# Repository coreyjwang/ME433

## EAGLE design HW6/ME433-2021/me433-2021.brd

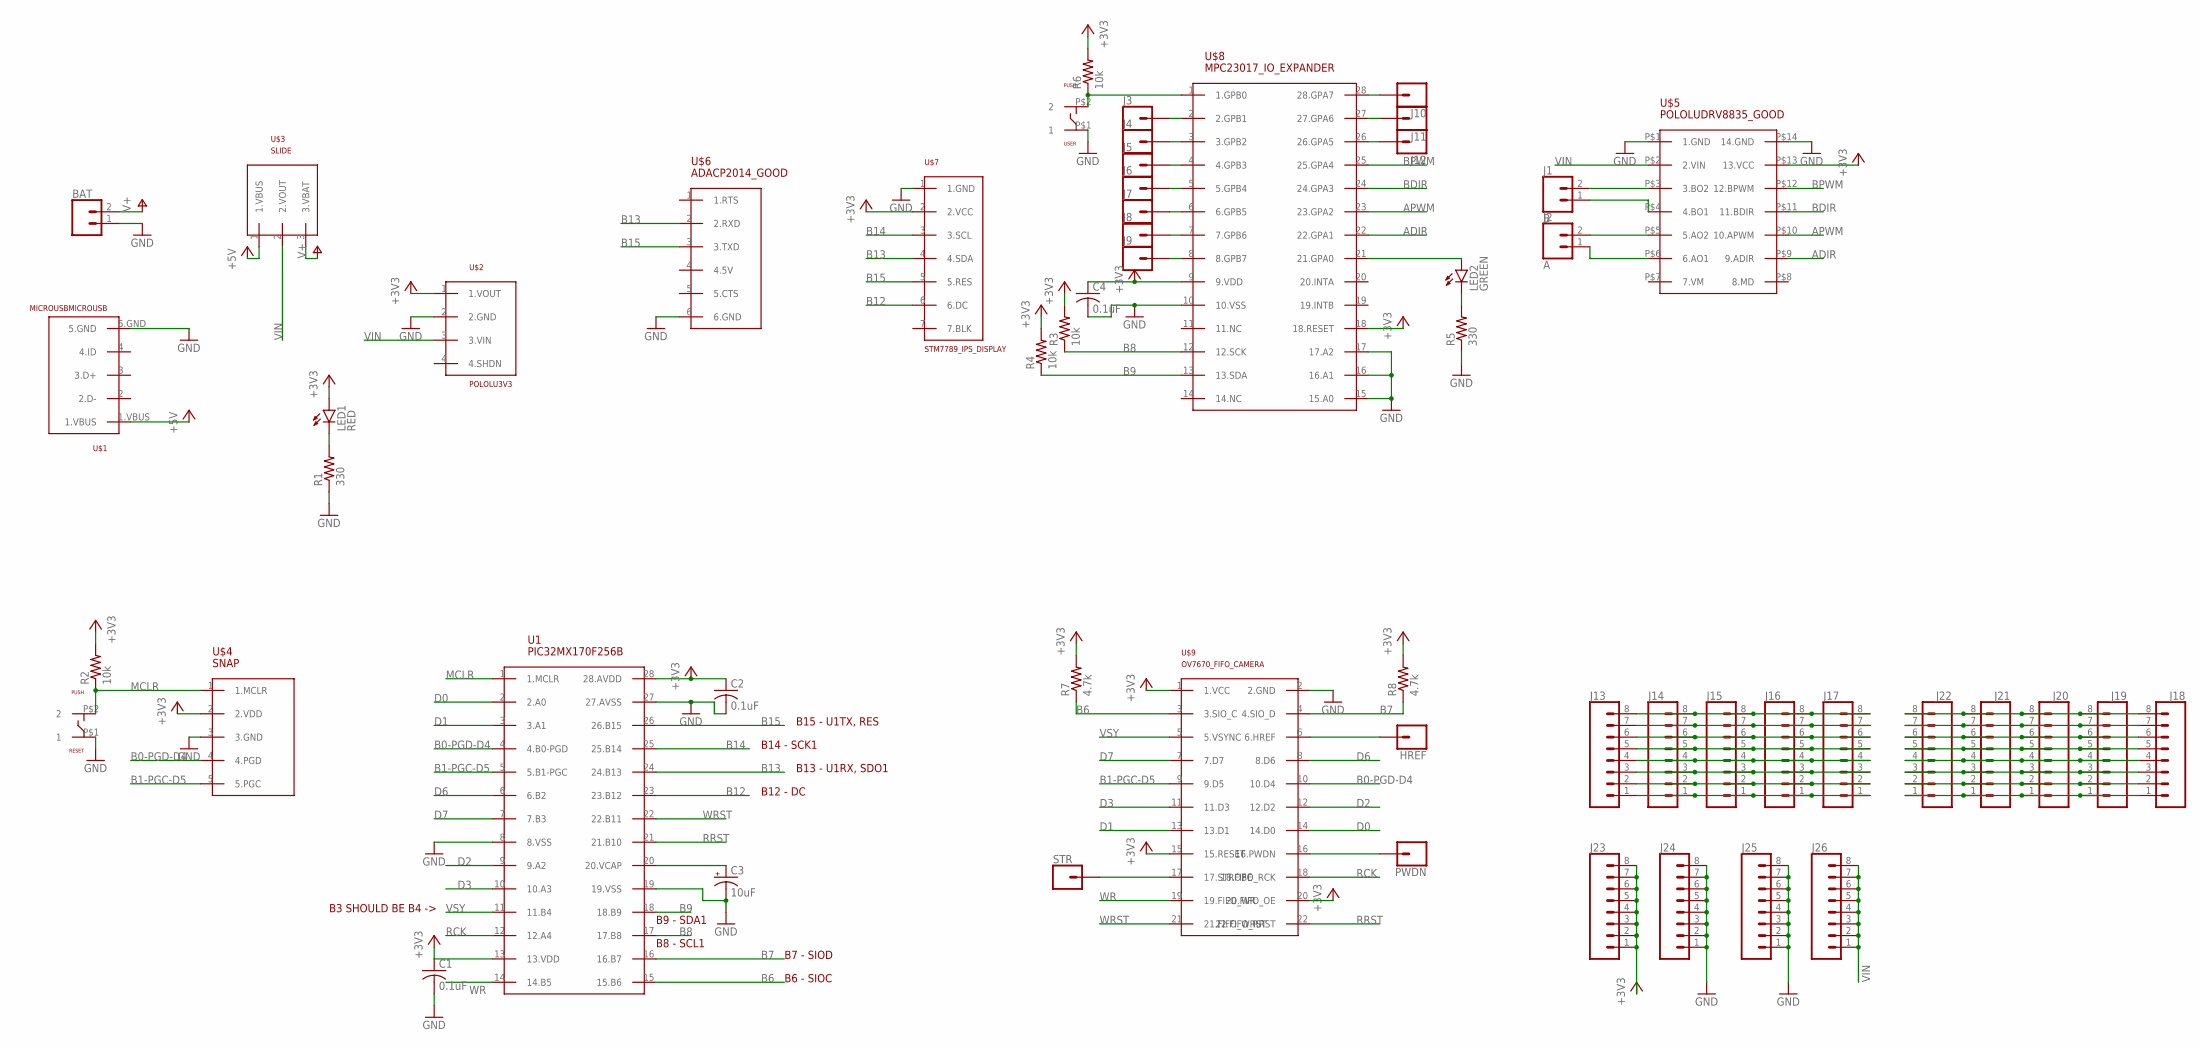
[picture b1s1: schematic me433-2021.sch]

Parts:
BAT: CONN_02; 1X02
C1, C2, C4: 0.1uF; C025-030X050
C3: 10uF; B45181B
HREF: CONN_01; 1X01
J1: B; 1X02
J2: A; 1X02
J3, J4, J5, J6, J7, J8, J9, J10, J11, J12: CONN_01; 1X01
J13, J14, J15, J16, J17, J18, J19, J20, J21, J22, J23, J24, J25, J26: CONN_08"; 1X08
LED1: RED; LED3MM
LED2: GREEN; LED3MM
PWDN: CONN_01; 1X01
R1, R5: 330; 0207/10
R2, R3, R4, R6: 10k; 0207/10
R7, R8: 4.7k; 0207/10
RESET: PUSH
STR: CONN_01; 1X01
U1: PIC32MX170F256B; DIL28-3
U$1: MICROUSBMICROUSB; MICROUSB
U$2: POLOLU3V3
U$3: SLIDE
U$4: SNAP; 1X05
U$5: POLOLUDRV8835_GOOD; POLOLU_DRV8835_H_BRIDGE_BREAKOUT
U$6: ADACP2014_GOOD; 1X06
U$7: STM7789_IPS_DISPLAY; 1X07
U$8: MPC23017_IO_EXPANDER; DIL28-3
U$9: OV7670_FIFO_CAMERA; 2X12
USER: PUSH

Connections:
+3V3: C2.1, C4.1, J23.1, J23.2, J23.3, J23.4, J23.5, J23.6, J23.7, J23.8, LED1.A, R2.2, R3.2, R4.2, R6.2, R7.2, R8.2, U1.28 (28.AVDD), U$2.1 (1.VOUT), U$4.2 (2.VDD), U$5.P$13 (13.VCC), U$7.2 (2.VCC), U$8.9 (9.VDD), U$8.18 (18.RESET), U$9.1 (1.VCC), U$9.15 (15.RESET), U$9.20 (20.FIFO_OE)
+5V: U$1.1.VBUS, U$3.1 (1.VBUS)
ADIR: U$5.P$9 (9.ADIR), U$8.22 (22.GPA1)
APWM: U$5.P$10 (10.APWM), U$8.23 (23.GPA2)
B0-PGD-D4: U1.4 (4.B0-PGD), U$4.4 (4.PGD), U$9.10 (10.D4)
B1-PGC-D5: U1.5 (5.B1-PGC), U$4.5 (5.PGC), U$9.9 (9.D5)
B6: R7.1, U1.15 (15.B6), U$9.3 (3.SIO_C)
B7: R8.1, U1.16 (16.B7), U$9.4 (4.SIO_D)
B8: R3.1, U1.17 (17.B8), U$8.12 (12.SCK)
B9: R4.1, U1.18 (18.B9), U$8.13 (13.SDA)
B12: U1.23 (23.B12), U$7.6 (6.DC)
B13: U1.24 (24.B13), U$6.2 (2.RXD), U$7.4 (4.SDA)
B14: U1.25 (25.B14), U$7.3 (3.SCL)
B15: U1.26 (26.B15), U$6.3 (3.TXD), U$7.5 (5.RES)
BDIR: U$5.P$11 (11.BDIR), U$8.24 (24.GPA3)
BPWM: U$5.P$12 (12.BPWM), U$8.25 (25.GPA4)
D0: U1.2 (2.A0), U$9.14 (14.D0)
D1: U1.3 (3.A1), U$9.13 (13.D1)
D2: U1.9 (9.A2), U$9.12 (12.D2)
D3: U1.10 (10.A3), U$9.11 (11.D3)
D6: U1.6 (6.B2), U$9.8 (8.D6)
D7: U1.7 (7.B3), U$9.7 (7.D7)
GND: BAT.1, C1.2, C2.2, C3.-, C4.2, J24.1, J24.2, J24.3, J24.4, J24.5, J24.6, J24.7, J24.8, J25.1, J25.2, J25.3, J25.4, J25.5, J25.6, J25.7, J25.8, R1.1, R5.1, RESET.P$1 (1), U1.8 (8.VSS), U1.19 (19.VSS), U1.27 (27.AVSS), U$1.5.GND, U$2.2 (2.GND), U$4.3 (3.GND), U$5.P$1 (1.GND), U$5.P$14 (14.GND), U$6.6 (6.GND), U$7.1 (1.GND), U$8.10 (10.VSS), U$8.15 (15.A0), U$8.16 (16.A1), U$8.17 (17.A2), U$9.2 (2.GND), USER.P$1 (1)
MCLR: R2.1, RESET.P$2 (2), U1.1 (1.MCLR), U$4.1 (1.MCLR)
unnamed: LED1.K (C), R1.2
unnamed: C1.1, U1.13 (13.VDD)
unnamed: C3.+, U1.20 (20.VCAP)
unnamed: J1.2, U$5.P$3 (3.BO2)
unnamed: J1.1, U$5.P$4 (4.BO1)
unnamed: J2.2, U$5.P$5 (5.AO2)
unnamed: LED2.A, U$8.21 (21.GPA0)
unnamed: LED2.K (C), R5.2
unnamed: R6.1, U$8.1 (1.GPB0), USER.P$2 (2)
unnamed: J2.1, U$5.P$6 (6.AO1)
unnamed: STR.1, U$9.17 (17.STROBE)
unnamed: PWDN.1, U$9.16 (16.PWDN)
unnamed: HREF.1, U$9.6 (6.HREF)
unnamed: J3.1, U$8.2 (2.GPB1)
unnamed: J4.1, U$8.3 (3.GPB2)
unnamed: J5.1, U$8.4 (4.GPB3)
unnamed: J6.1, U$8.5 (5.GPB4)
unnamed: J7.1, U$8.6 (6.GPB5)
unnamed: J8.1, U$8.7 (7.GPB6)
unnamed: J9.1, U$8.8 (8.GPB7)
unnamed: J10.1, U$8.28 (28.GPA7)
unnamed: J11.1, U$8.27 (27.GPA6)
unnamed: J12.1, U$8.26 (26.GPA5)
unnamed: J13.8, J14.8, J15.8, J16.8, J17.8
unnamed: J13.7, J14.7, J15.7, J16.7, J17.7
unnamed: J13.6, J14.6, J15.6, J16.6, J17.6
unnamed: J13.5, J14.5, J15.5, J16.5, J17.5
unnamed: J13.4, J14.4, J15.4, J16.4, J17.4
unnamed: J13.3, J14.3, J15.3, J16.3, J17.3
unnamed: J13.2, J14.2, J15.2, J16.2, J17.2
unnamed: J13.1, J14.1, J15.1, J16.1, J17.1
unnamed: J18.8, J19.8, J20.8, J21.8, J22.8
unnamed: J18.7, J19.7, J20.7, J21.7, J22.7
unnamed: J18.6, J19.6, J20.6, J21.6, J22.6
unnamed: J18.5, J19.5, J20.5, J21.5, J22.5
unnamed: J18.4, J19.4, J20.4, J21.4, J22.4
unnamed: J18.3, J19.3, J20.3, J21.3, J22.3
unnamed: J18.2, J19.2, J20.2, J21.2, J22.2
unnamed: J18.1, J19.1, J20.1, J21.1, J22.1
RCK: U1.12 (12.A4), U$9.18 (18.FIFO_RCK)
RRST: U1.21 (21.B10), U$9.22 (22.FIFO_RRST)
V+: BAT.2, U$3.3 (3.VBAT)
VIN: J26.1, J26.2, J26.3, J26.4, J26.5, J26.6, J26.7, J26.8, U$2.3 (3.VIN), U$3.2 (2.VOUT), U$5.P$2 (2.VIN)
VSY: U1.11 (11.B4), U$9.5 (5.VSYNC)
WR: U1.14 (14.B5), U$9.19 (19.FIFO_WR)
WRST: U1.22 (22.B11), U$9.21 (21.FIFO_WRST)

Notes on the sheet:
B15 - U1TX, RES
B13 - U1RX, SDO1
B14 - SCK1
B12 - DC
B9 - SDA1
B8 - SCL1
B7 - SIOD
B6 - SIOC
B3 SHOULD BE B4 ->

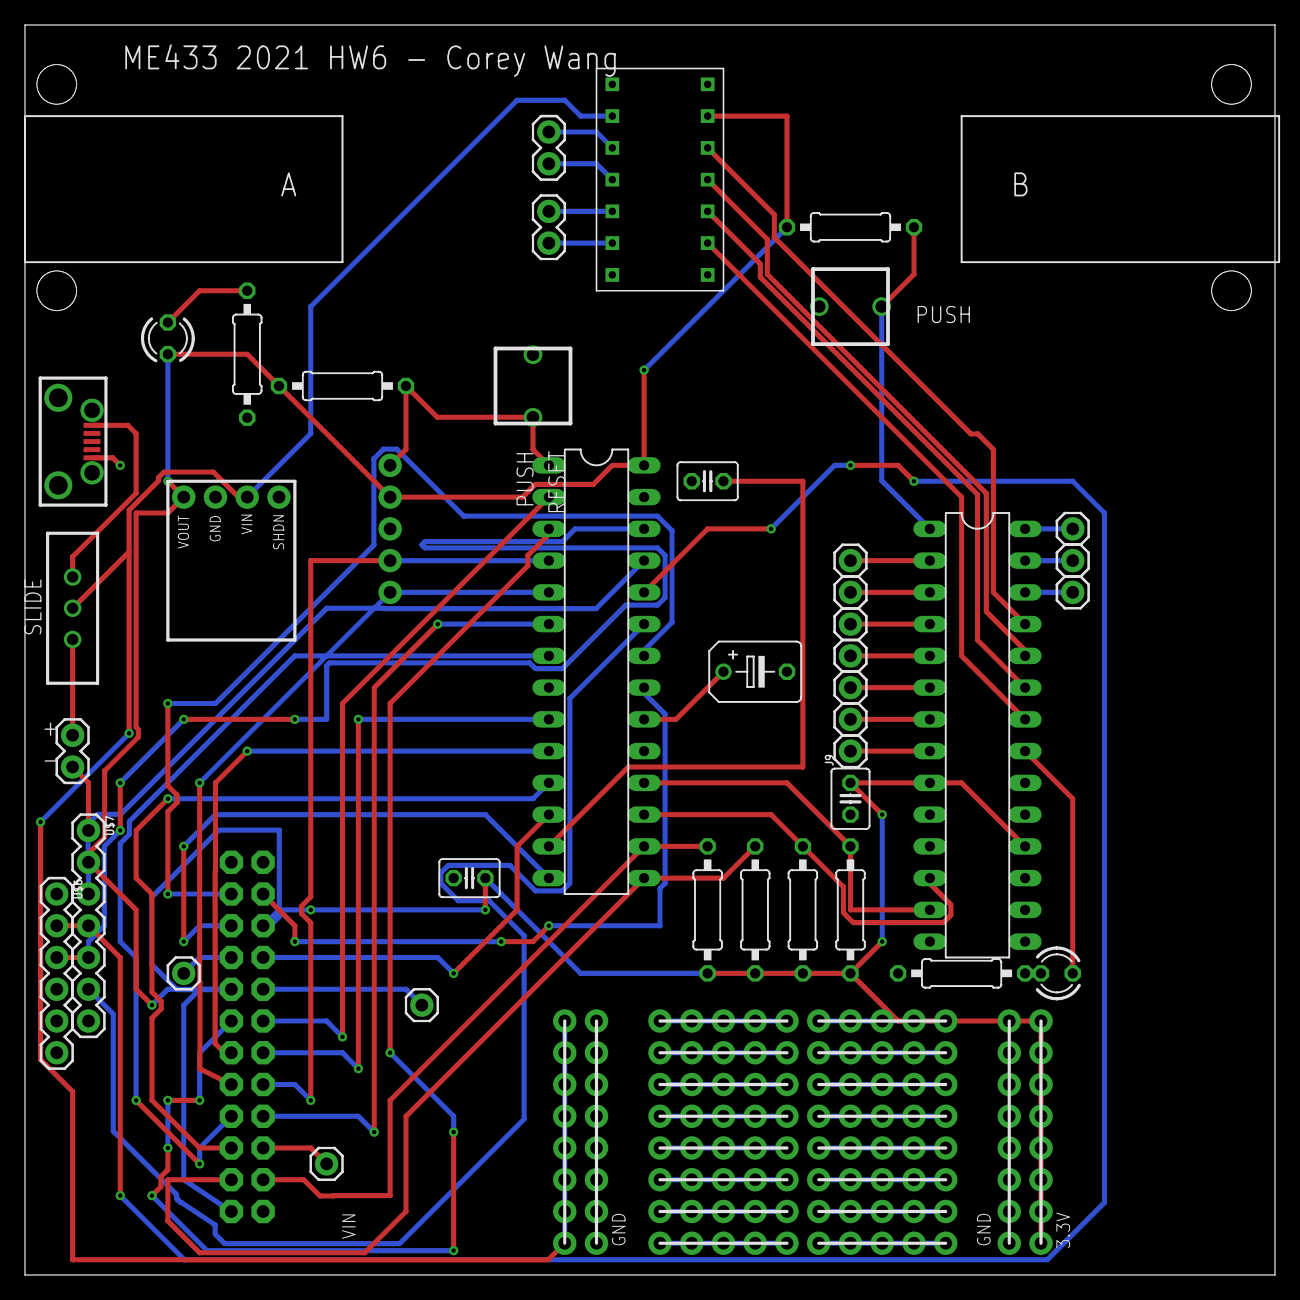
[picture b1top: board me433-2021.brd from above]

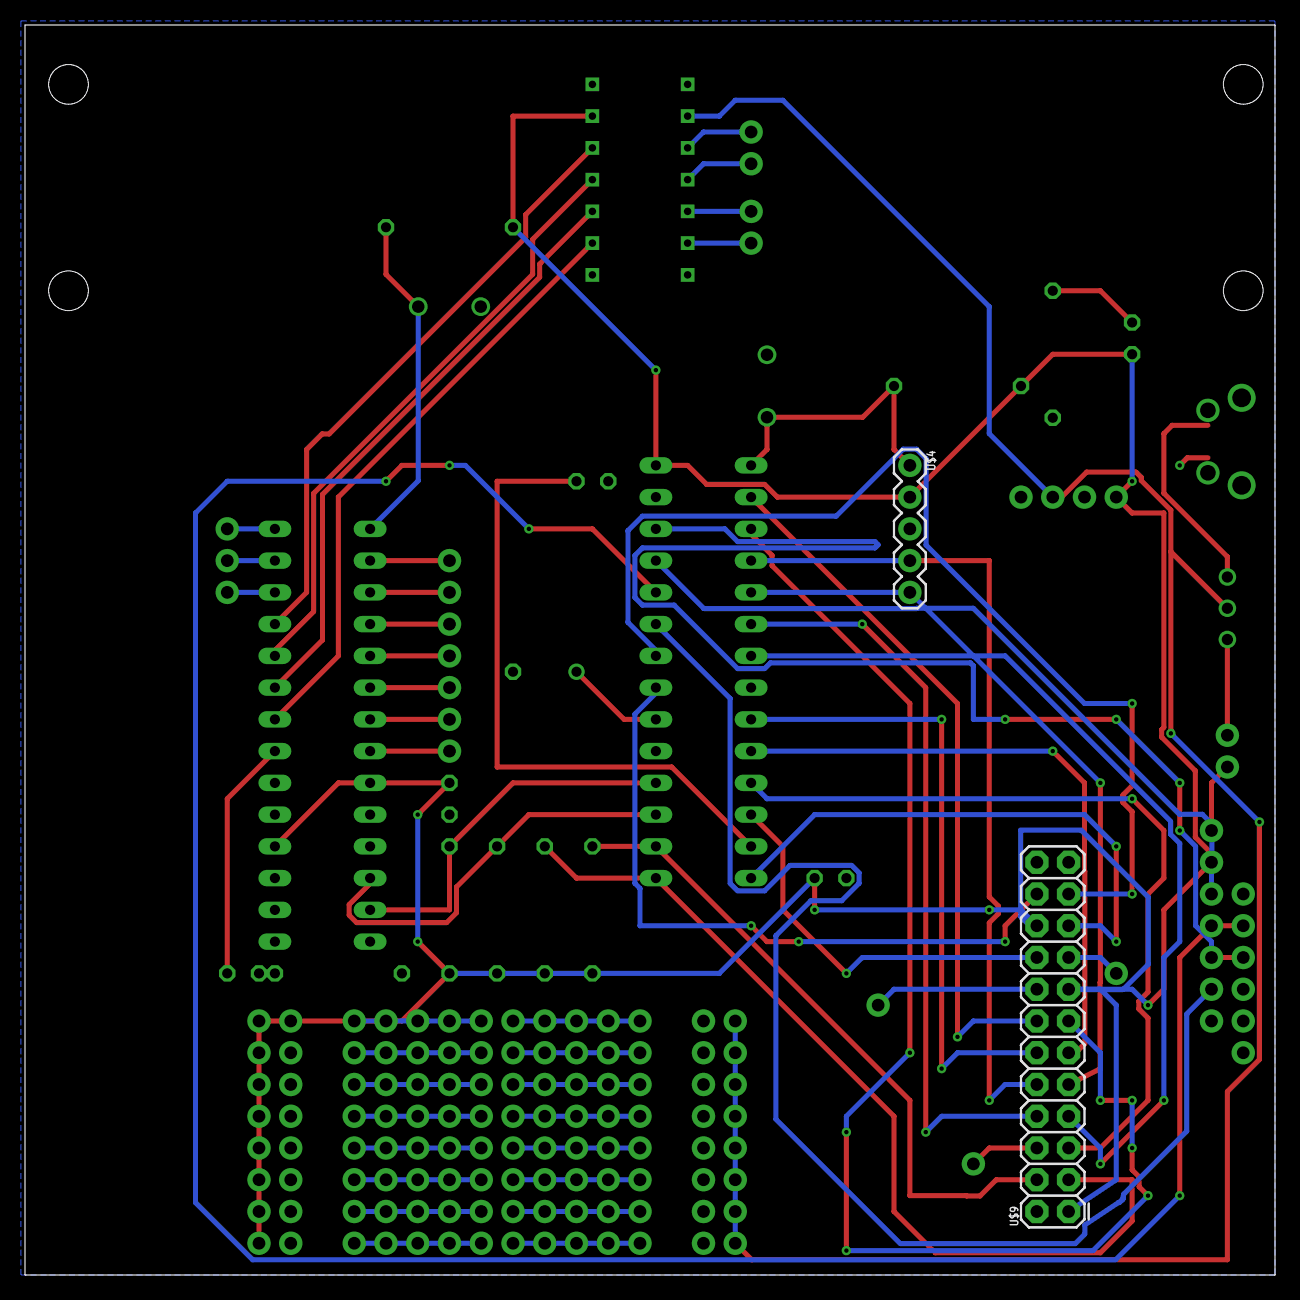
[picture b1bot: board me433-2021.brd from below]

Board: 2 copper layers, 100.0 x 100.0 mm, 56 parts (2 on the bottom side), 70 nets.

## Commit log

2021-04-06 Completed first time
2021-04-06 Fixed 6 and 7
2021-04-08 Fixed problem 7 after watching video
2021-04-12 HW3 - Lab kit image
2021-04-15 Completed HW4 code and images
2021-04-20 Folders for upcoming HW
2021-04-21 Completed HW5
2021-06-12 Completed HW7
2021-09-19 HW6 2/3
    Backup copy of project after completing second video, will delete and replace with complete project at the end
2021-09-21 Completed HW6
    Completed HW6 with screenshots of schematic and board
2021-09-24 Completed HW8
2021-10-02 Completed HW9 and HW16
2021-10-02 Small change to HW9 and Part of HW11
2021-10-03 Completed HW11
2021-10-04 Completed HW14
